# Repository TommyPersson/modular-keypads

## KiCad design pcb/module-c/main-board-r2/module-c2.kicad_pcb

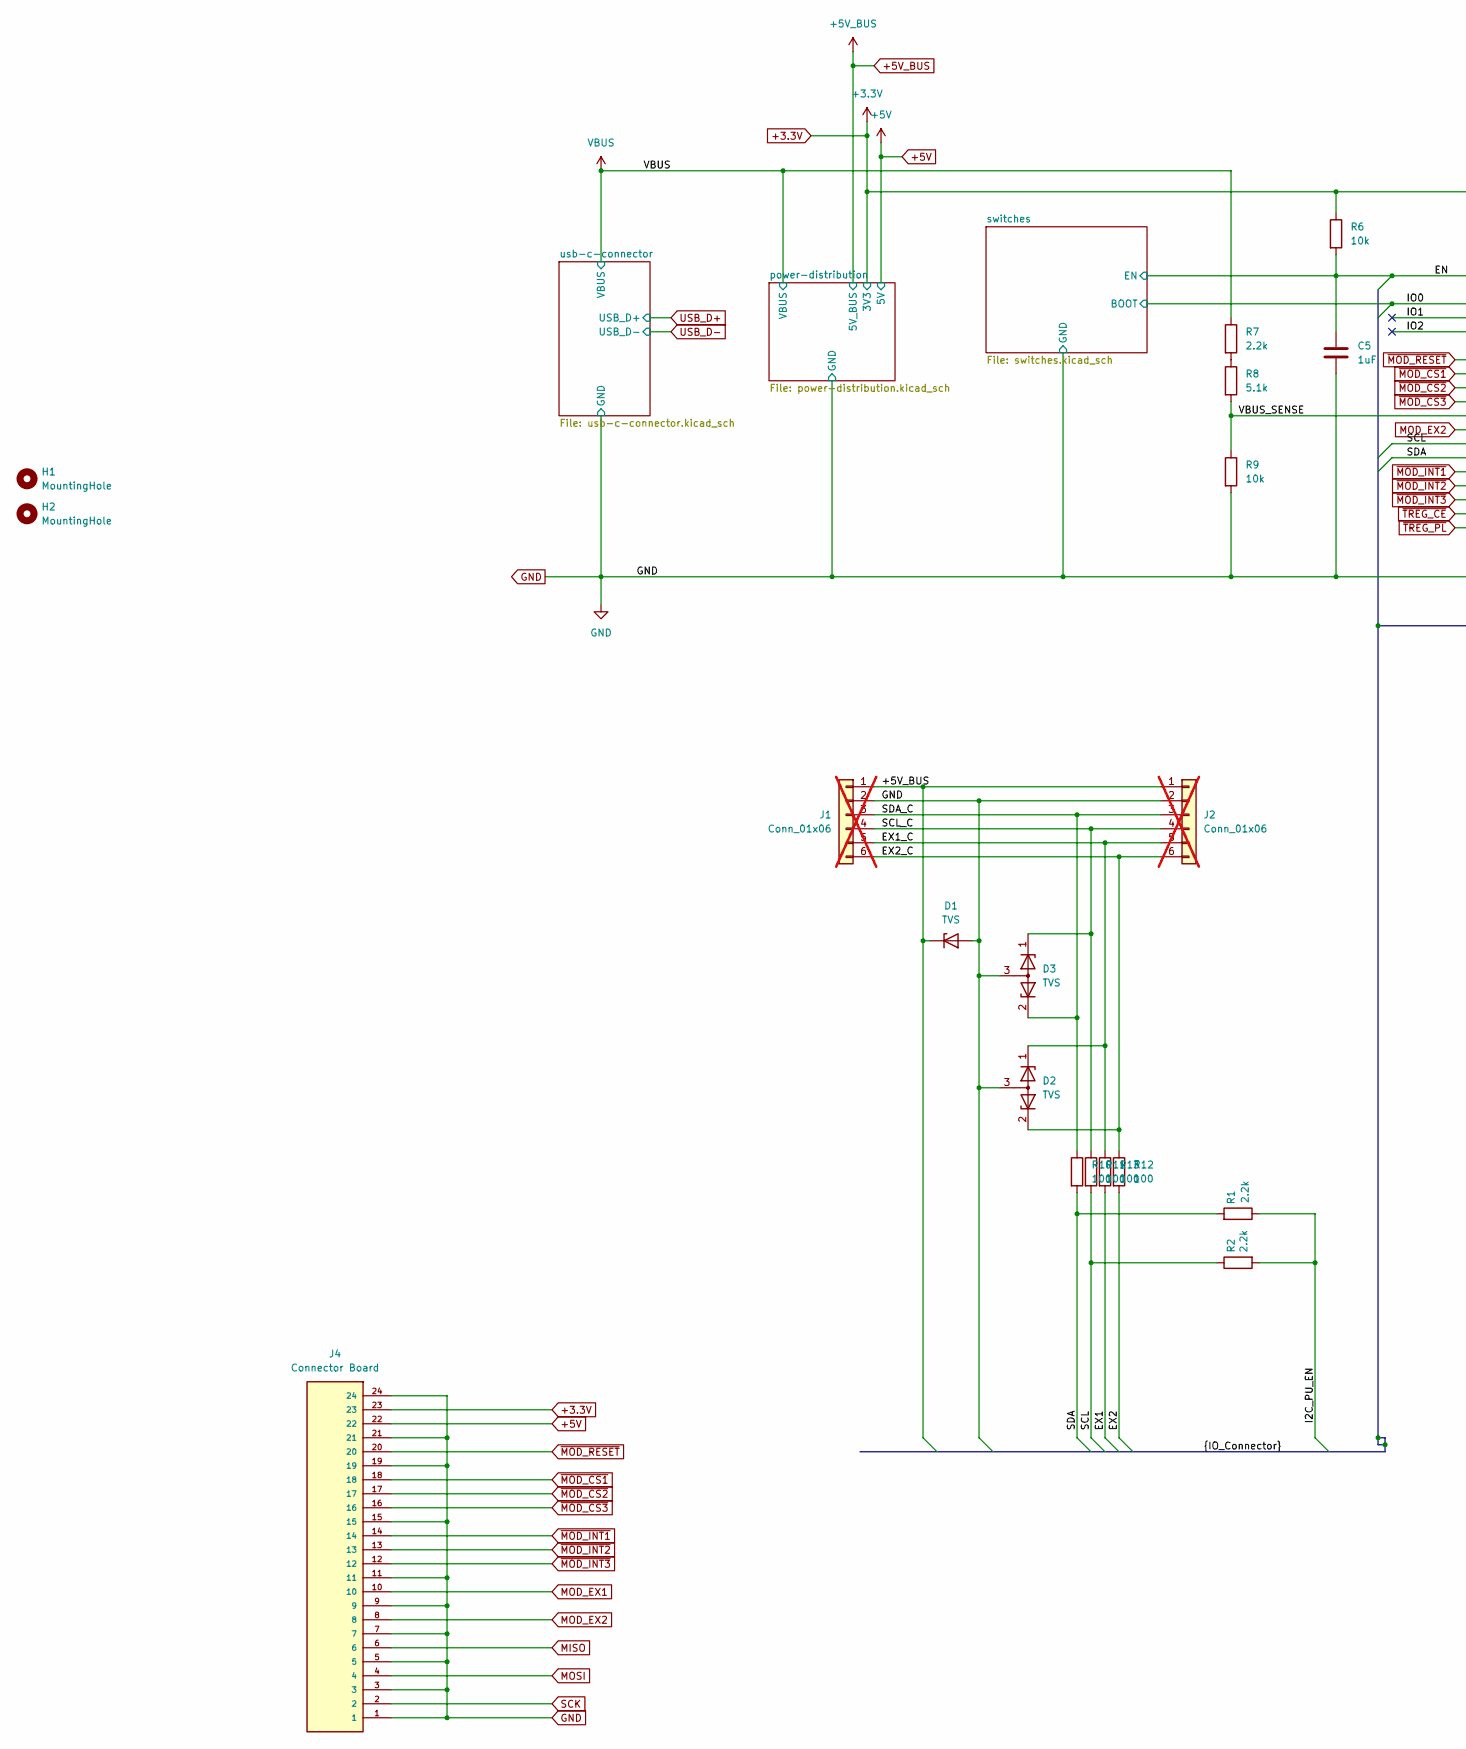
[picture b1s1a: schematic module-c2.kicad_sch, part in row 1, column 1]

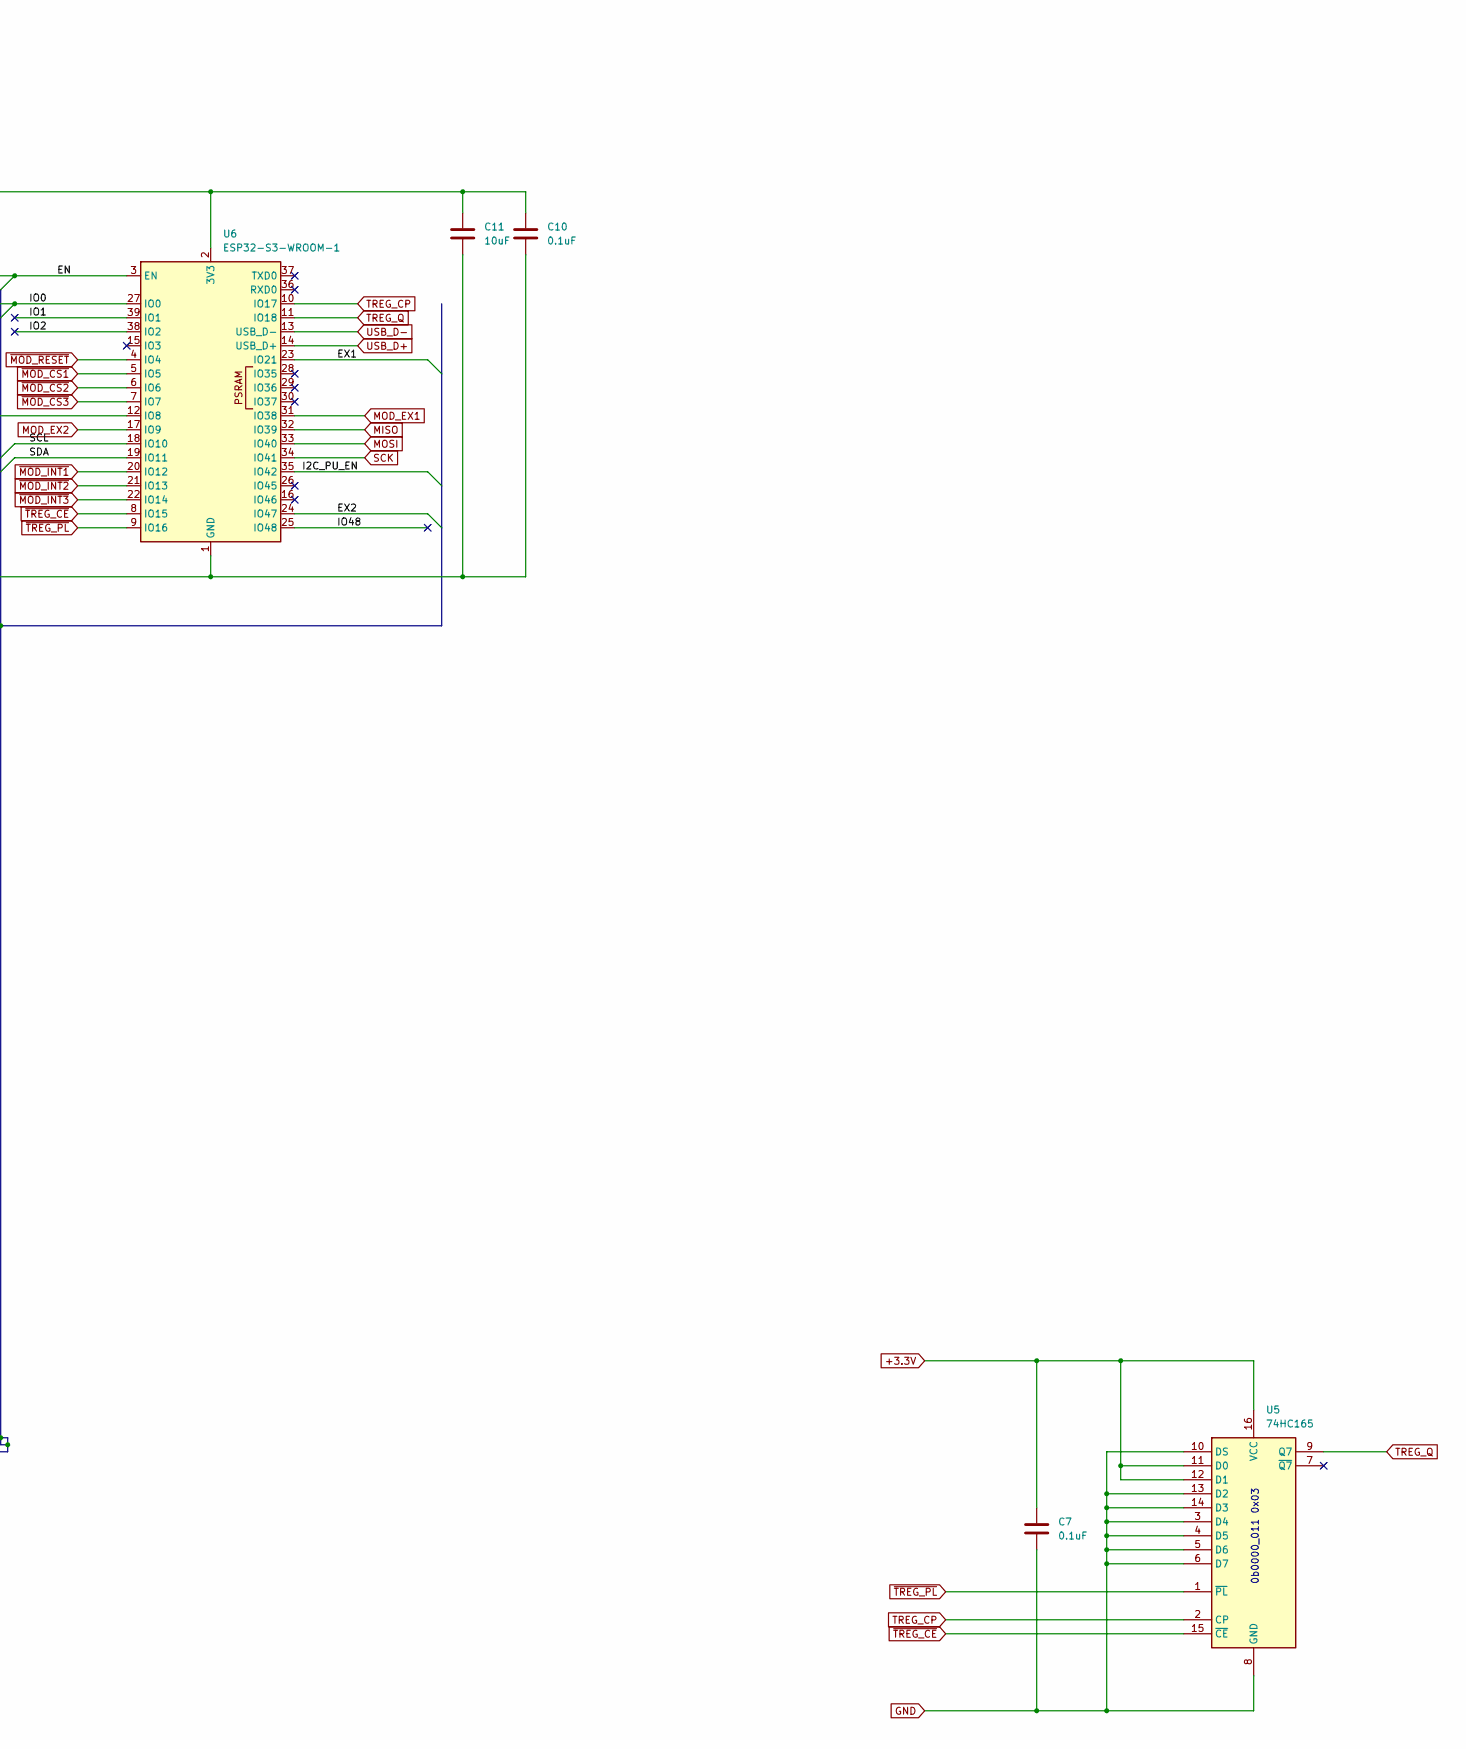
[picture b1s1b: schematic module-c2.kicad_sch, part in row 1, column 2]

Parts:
C5: 1uF; C_0805_2012Metric
C7, C10: 0.1uF; C_0603_1608Metric
C11: 10uF; C_0805_2012Metric
D1: TVS; Nexperia_CFP3_SOD-123W
D2, D3: TVS; SOT-723
H1, H2: MountingHole; MountingHole_2.2mm_M2
J1: Conn_01x06; PinSocket_1x06_P2.54mm_MagPogoHor_R; not fitted
J2: Conn_01x06; PinSocket_1x06_P2.54mm_MagPogoHor; not fitted
J4: Connector Board; AMPHENOL_F3311A7H121024E200; PARTREV A
R1, R2, R7: 2.2k; R_0603_1608Metric
R6, R9: 10k; R_0603_1608Metric
R8: 5.1k; R_0603_1608Metric
R10, R11, R12, R13: 100; R_0603_1608Metric
U5: 74HC165; DHVQFN-16-1EP_2.5x3.5mm_P0.5mm_EP1x2mm
U6: ESP32-S3-WROOM-1; ESP32-S3-WROOM-1U

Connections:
+3.3V: C7.1, C10.1, C11.1, J4.23, R6.1, U5.11 (D0), U5.12 (D1), U5.16 (VCC), U6.2 (3V3); also elsewhere on the board
+5V: J4.22; also elsewhere on the board
+5V_BUS: D1.1 (K), J1.1, J2.1; also elsewhere on the board
/EN: C5.1, R6.2, U6.3 (EN); also elsewhere on the board
/EX1: R13.2, U6.23 (IO21)
/EX1_C: D2.1 (K), J1.5, J2.5, R13.1
/EX2: R12.2, U6.24 (IO47)
/EX2_C: D2.2 (K), J1.6, J2.6, R12.1
/I2C_PU_EN: R1.1, R2.2, U6.35 (IO42)
/IO0: U6.27 (IO0); also elsewhere on the board
/IO1: U6.39 (IO1)
/IO2: U6.38 (IO2)
/IO48: U6.25 (IO48)
/SCL: R2.1, R11.2, U6.18 (IO10)
/SCL_C: D3.1 (K), J1.4, J2.4, R11.1
/SDA: R1.2, R10.2, U6.19 (IO11)
/SDA_C: D3.2 (K), J1.3, J2.3, R10.1
/VBUS_SENSE: R8.2, R9.1, U6.12 (IO8)
GND: C5.2, C7.2, C10.2, C11.2, D1.2 (A), D2.3 (A), D3.3 (A), J1.2, J2.2, J4.1, J4.3, J4.5, J4.7, J4.9, J4.11, J4.15, J4.19, J4.21, J4.24, R9.2, U5.3 (D4), U5.4 (D5), U5.5 (D6), U5.6 (D7), U5.8 (GND), U5.10 (DS), U5.13 (D2), U5.14 (D3), U6.1 (GND), U6.40 (GND), U6.41 (GND); also elsewhere on the board
MISO: J4.6, U6.32 (IO39)
MOD_EX1: J4.10, U6.31 (IO38)
MOD_EX2: J4.8, U6.17 (IO9)
MOSI: J4.4, U6.33 (IO40)
unnamed: R7.2, R8.1
SCK: J4.2, U6.34 (IO41)
TREG_CP: U5.2 (CP), U6.10 (IO17)
TREG_Q: U5.9 (Q7), U6.11 (IO18)
USB_D+: U6.14 (USB_D+); also elsewhere on the board
USB_D-: U6.13 (USB_D-); also elsewhere on the board
VBUS: R7.1; also elsewhere on the board
~MOD_CS1: J4.18, U6.5 (IO5)
~MOD_CS2: J4.17, U6.6 (IO6)
~MOD_CS3: J4.16, U6.7 (IO7)
~MOD_INT1: J4.14, U6.20 (IO12)
~MOD_INT2: J4.13, U6.21 (IO13)
~MOD_INT3: J4.12, U6.22 (IO14)
~MOD_RESET: J4.20, U6.4 (IO4)
~TREG_CE: U5.15 (~CE), U6.8 (IO15)
~TREG_PL: U5.1 (~PL), U6.9 (IO16)

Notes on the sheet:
0b0000_011 0x03

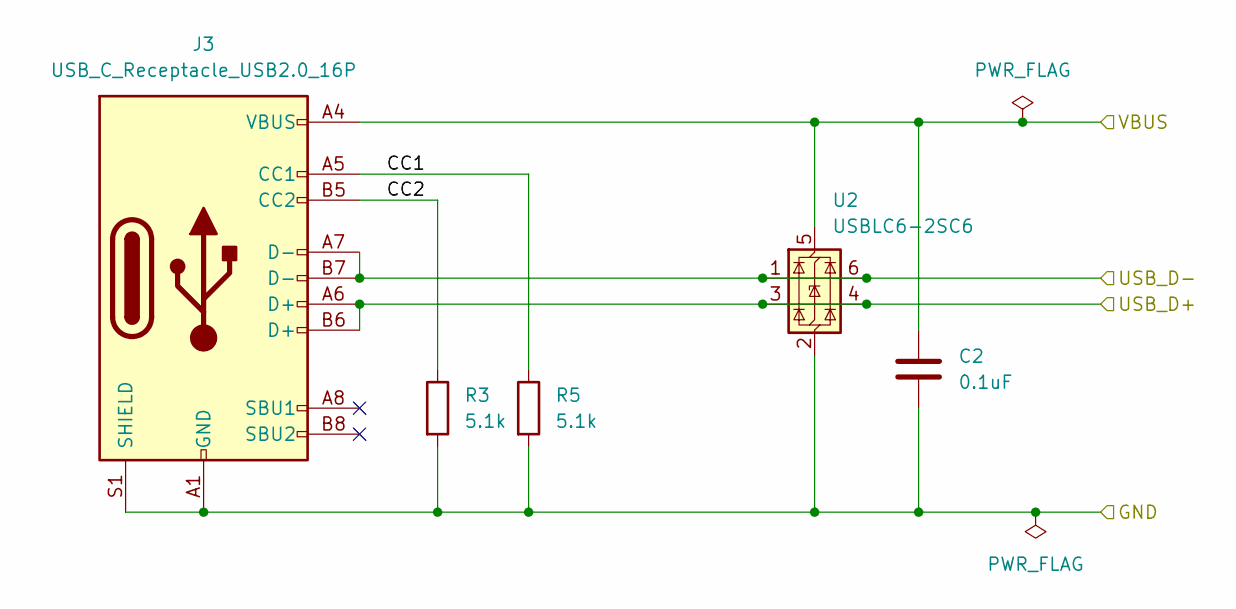
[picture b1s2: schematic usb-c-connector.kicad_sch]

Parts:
C2: 0.1uF; C_0603_1608Metric
J3: USB_C_Receptacle_USB2.0_16P; USB_C_Receptacle_GCT_USB4105-xx-A_16P_TopMnt_Horizontal
R3, R5: 5.1k; R_0603_1608Metric
U2: USBLC6-2SC6; SOT-23-6_Handsoldering

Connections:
/usb-c-connector/CC1: J3.A5 (CC1), R5.1
/usb-c-connector/CC2: J3.B5 (CC2), R3.1
GND: C2.2, J3.A1 (GND), J3.A12 (GND), J3.B1 (GND), J3.B12 (GND), J3.S1 (SHIELD), R3.2, R5.2, U2.2 (GND); also elsewhere on the board
USB_D+: J3.A6 (D+), J3.B6 (D+), U2.3 (I/O2), U2.4 (I/O2); also elsewhere on the board
USB_D-: J3.A7 (D-), J3.B7 (D-), U2.1 (I/O1), U2.6 (I/O1); also elsewhere on the board
VBUS: C2.1, J3.A4 (VBUS), J3.A9 (VBUS), J3.B4 (VBUS), J3.B9 (VBUS), U2.5 (VBUS); also elsewhere on the board

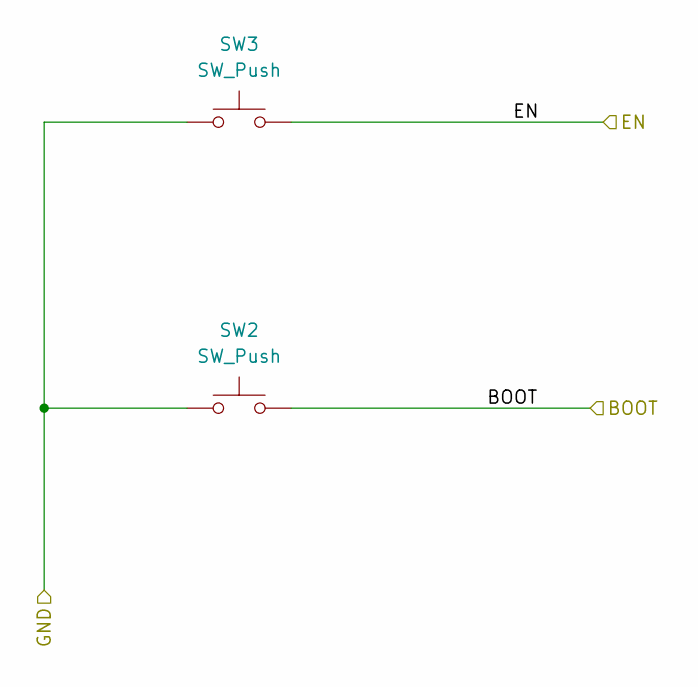
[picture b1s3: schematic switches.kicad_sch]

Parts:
SW2, SW3: SW_Push; Panasonic_EVQPUL_EVQPUC

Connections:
/EN: SW3.2; also elsewhere on the board
/IO0: SW2.2; also elsewhere on the board
GND: SW2.1, SW3.1; also elsewhere on the board

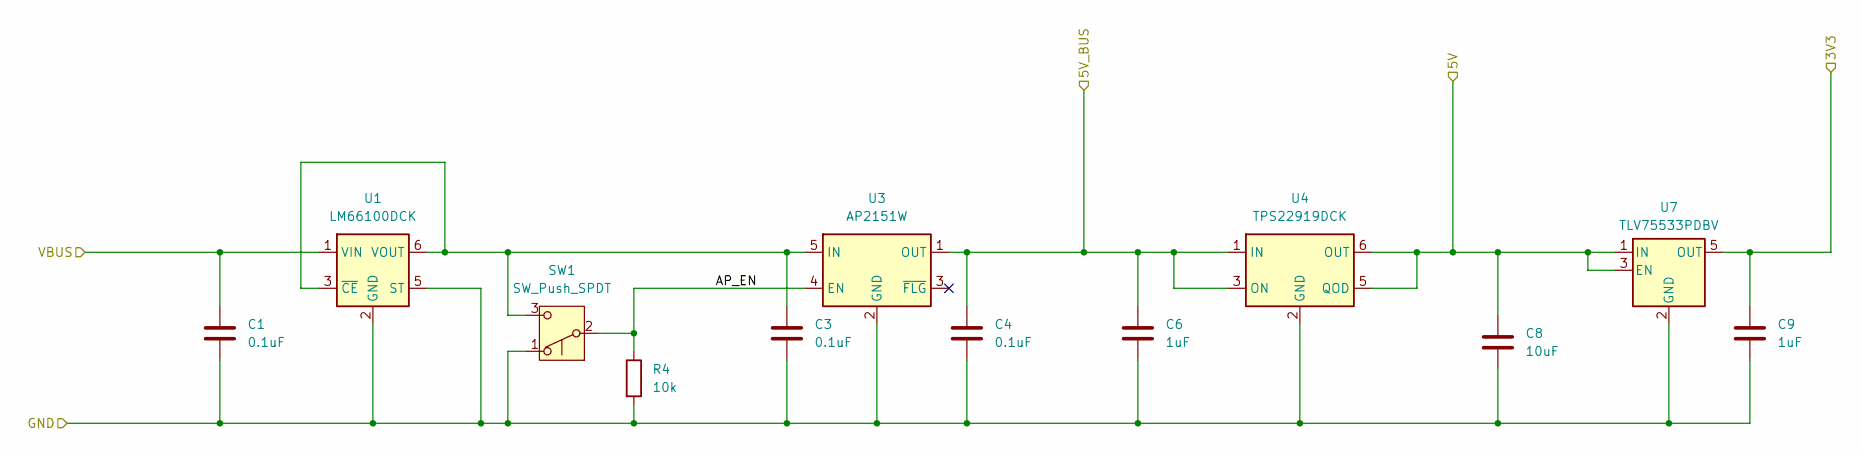
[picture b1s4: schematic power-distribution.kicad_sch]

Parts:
C1, C3, C4: 0.1uF; C_0603_1608Metric
C6, C9: 1uF; C_0805_2012Metric
C8: 10uF; C_0805_2012Metric
R4: 10k; R_0603_1608Metric
SW1: SW_Push_SPDT; SW_MSK12C02-HB
U1: LM66100DCK; SOT-363_SC-70-6
U3: AP2151W; SOT-23-5_HandSoldering
U4: TPS22919DCK; SOT-363_SC-70-6
U7: TLV75533PDBV; SOT-23-5

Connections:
+3.3V: C9.1, U7.5 (OUT); also elsewhere on the board
+5V: C8.1, U4.5 (QOD), U4.6 (OUT), U7.1 (IN), U7.3 (EN); also elsewhere on the board
+5V_BUS: C4.1, C6.1, U3.1 (OUT), U4.1 (IN), U4.3 (ON); also elsewhere on the board
/power-distribution/AP_EN: R4.1, SW1.2 (B), U3.4 (EN)
GND: C1.2, C3.2, C4.2, C6.2, C8.2, C9.2, R4.2, SW1.1 (A), U1.2 (GND), U1.5 (ST), U3.2 (GND), U4.2 (GND), U7.2 (GND); also elsewhere on the board
unnamed: C3.1, SW1.3 (C), U1.3 (~CE), U1.6 (VOUT), U3.5 (IN)
VBUS: C1.1, U1.1 (VIN); also elsewhere on the board

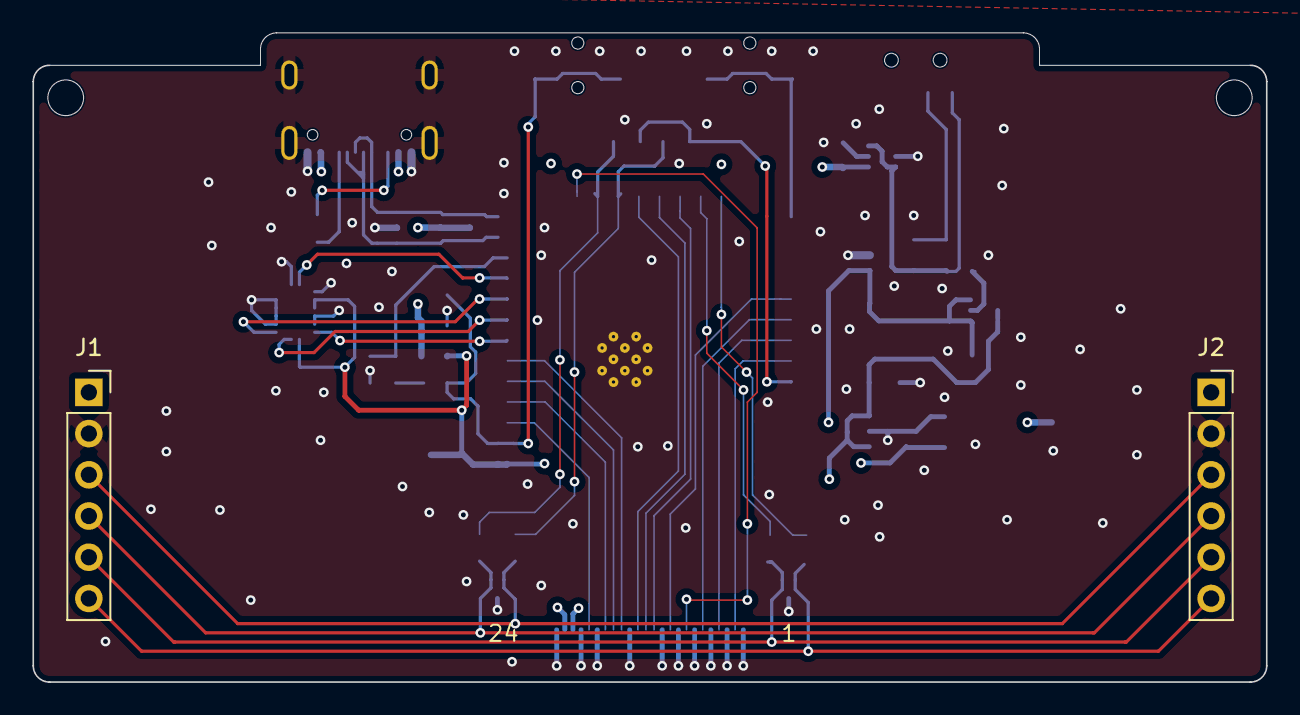
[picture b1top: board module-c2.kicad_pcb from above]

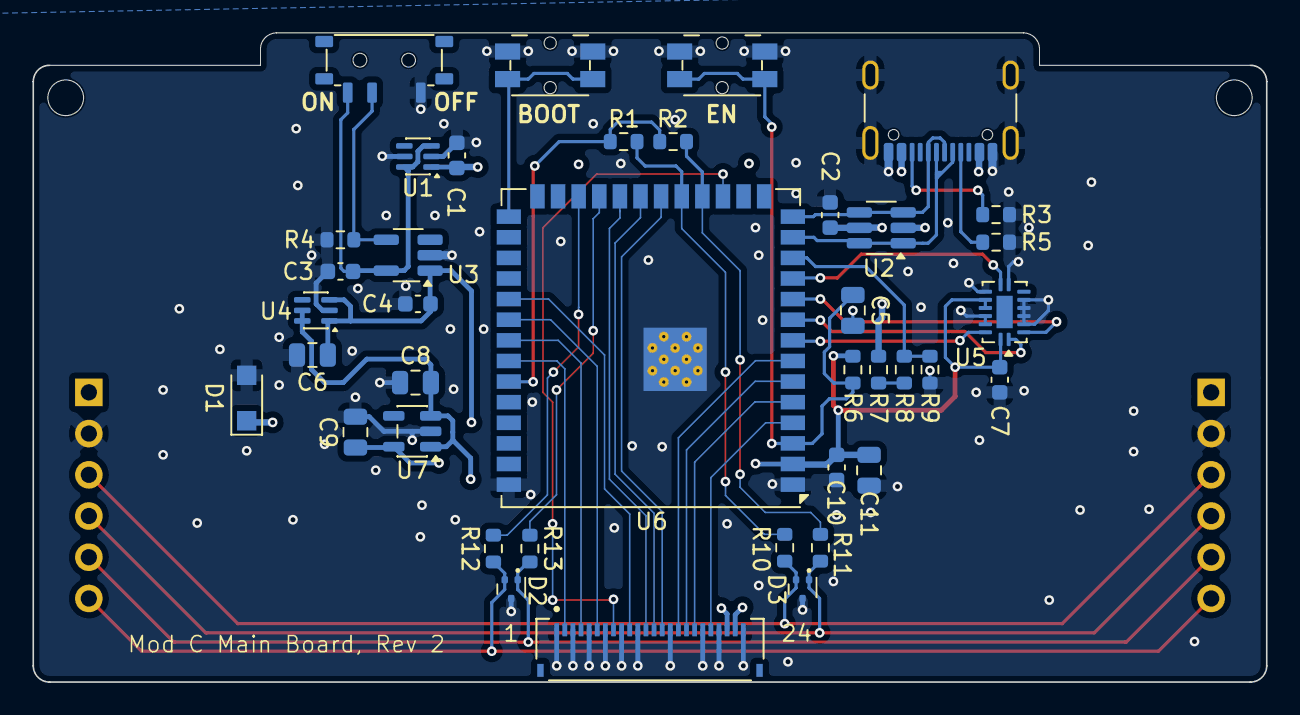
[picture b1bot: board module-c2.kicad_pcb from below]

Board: 4 copper layers, 76.0 x 40.0 mm, 43 parts (39 on the bottom side), 40 nets.

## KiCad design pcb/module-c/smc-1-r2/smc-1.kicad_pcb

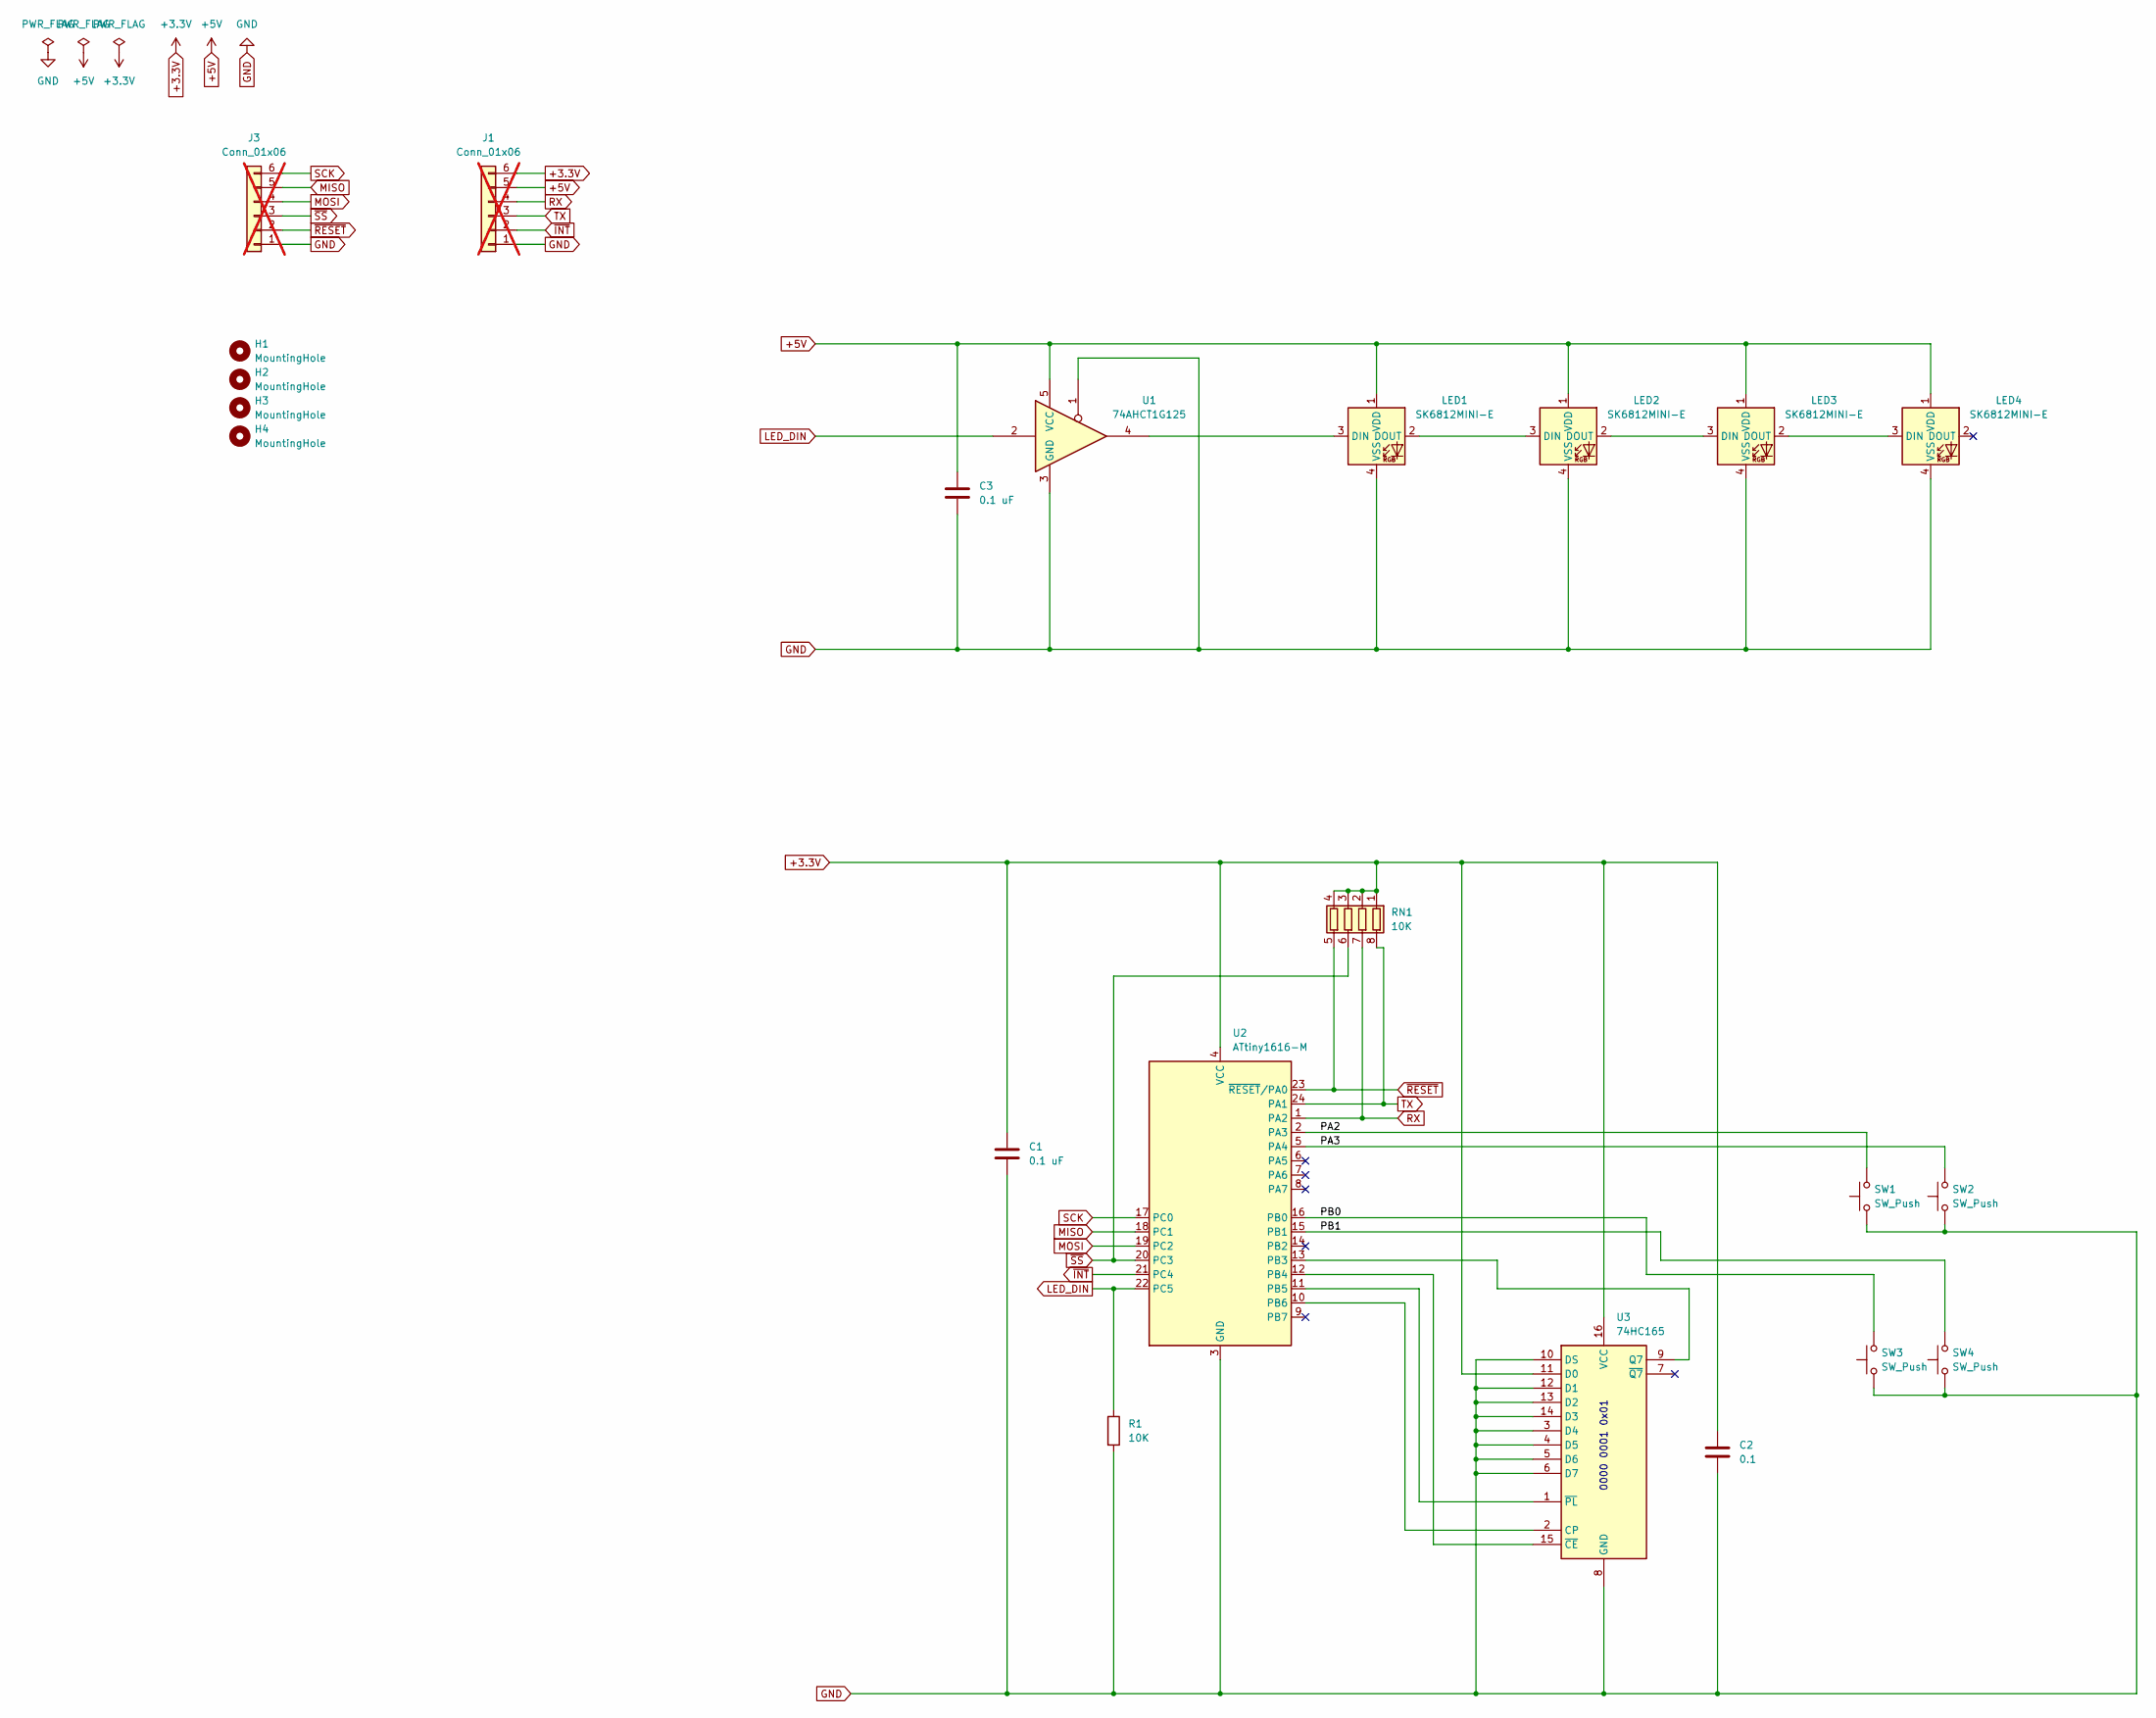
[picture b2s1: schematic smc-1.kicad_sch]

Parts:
C1, C3: 0.1 uF; C_0603_1608Metric
C2: 0.1; C_0603_1608Metric
H1, H2, H3, H4: MountingHole; MountingHole_2.2mm_M2
J1, J3: Conn_01x06; PinHeader_1x06_P2.54mm_Vertical; not fitted
LED1, LED2, LED3, LED4: SK6812MINI-E; LED_choc_6028R-ROT
R1: 10K; R_0603_1608Metric
RN1: 10K; R_Array_Concave_4x0603
SW1, SW2, SW3, SW4: SW_Push; SW_Hotswap_Kailh_Choc_V1_1.50u
U1: 74AHCT1G125; SOT-353_SC-70-5
U2: ATtiny1616-M; QFN-24-1EP_4x4mm_P0.5mm_EP2.6x2.6mm
U3: 74HC165; DHVQFN-16-1EP_2.5x3.5mm_P0.5mm_EP1x2mm

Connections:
+3.3V: C1.1, C2.1, J1.6, RN1.1 (R1.1), RN1.2 (R2.1), RN1.3 (R3.1), RN1.4 (R4.1), U2.4 (VCC), U3.11 (D0), U3.16 (VCC)
+5V: C3.1, J1.5, LED1.1 (VDD), LED2.1 (VDD), LED3.1 (VDD), LED4.1 (VDD), U1.5 (VCC)
/PA2: SW1.2, U2.2 (PA3)
/PA3: SW2.2, U2.5 (PA4)
/PB0: SW3.2, U2.16 (PB0)
/PB1: SW4.2, U2.15 (PB1)
GND: C1.2, C2.2, C3.2, J1.1, J3.1, LED1.4 (VSS), LED2.4 (VSS), LED3.4 (VSS), LED4.4 (VSS), R1.2, SW1.1, SW2.1, SW3.1, SW4.1, U1.1, U1.3 (GND), U2.3 (GND), U2.25 (GND), U3.3 (D4), U3.4 (D5), U3.5 (D6), U3.6 (D7), U3.8 (GND), U3.10 (DS), U3.12 (D1), U3.13 (D2), U3.14 (D3)
LED_DIN: R1.1, U1.2, U2.22 (PC5)
MISO: J3.5, U2.18 (PC1)
MOSI: J3.4, U2.19 (PC2)
unnamed: LED1.3 (DIN), U1.4
unnamed: LED1.2 (DOUT), LED2.3 (DIN)
unnamed: LED2.2 (DOUT), LED3.3 (DIN)
unnamed: LED3.2 (DOUT), LED4.3 (DIN)
unnamed: U2.13 (PB3), U3.9 (Q7)
unnamed: U2.12 (PB4), U3.15 (~CE)
unnamed: U2.11 (PB5), U3.1 (~PL)
unnamed: U2.10 (PB6), U3.2 (CP)
RX: J1.4, RN1.7 (R2.2), U2.1 (PA2)
SCK: J3.6, U2.17 (PC0)
TX: J1.3, RN1.8 (R1.2), U2.24 (PA1)
~INT: J1.2, U2.21 (PC4)
~RESET: J3.2, RN1.5 (R4.2), U2.23 (~RESET/PA0)
~SS: J3.3, RN1.6 (R3.2), U2.20 (PC3)

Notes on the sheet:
0000 0001 0x01

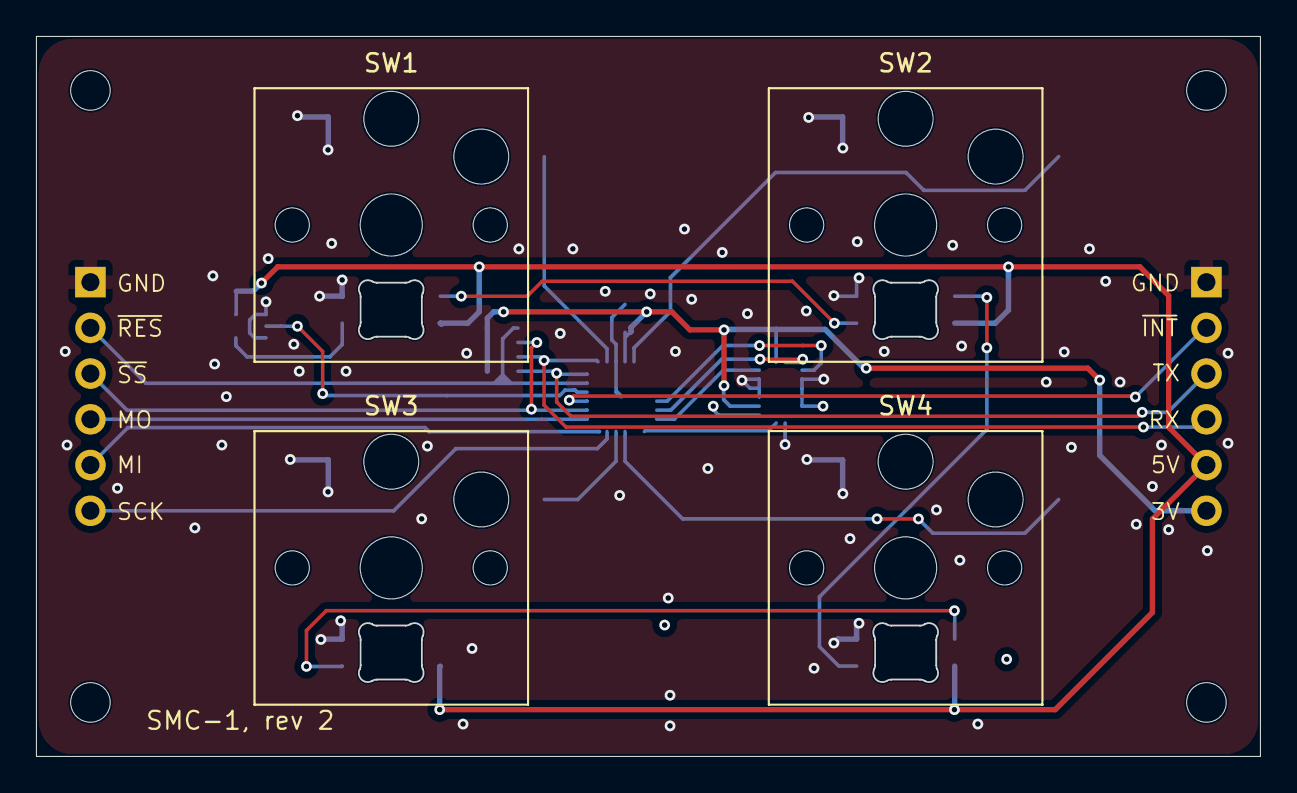
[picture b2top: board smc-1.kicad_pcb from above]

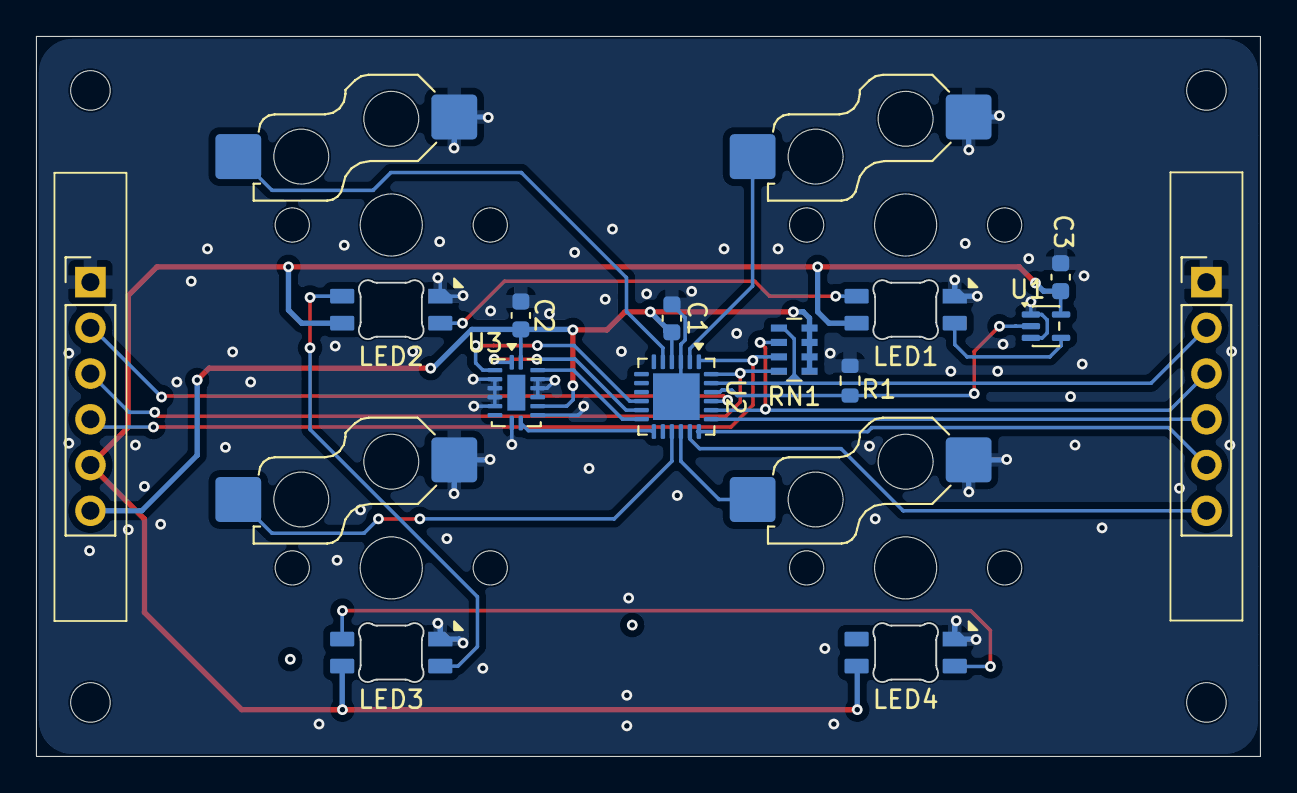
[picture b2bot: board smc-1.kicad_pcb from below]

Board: 4 copper layers, 68.0 x 40.0 mm, 22 parts (14 on the bottom side), 24 nets.

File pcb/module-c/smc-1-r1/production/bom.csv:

Designator,Footprint,Quantity,Value,LCSC Part #
"C1, C2",0603,2,0.1,
C3,0603,1,0.1 uF,
"J1, J3",PinHeader_1x06_P2.54mm_Vertical,2,Conn_01x06,
"LED1, LED2, LED3, LED4, LED5, LED6",LED_choc_6028R-ROT,6,SK6812MINI-E,
"SW1, SW2, SW3, SW4, SW5, SW6",SW_Hotswap_Kailh_Choc_V1_1.00u,6,SW_Push,
U1,SOT-353_SC-70-5,1,74AHCT1G125,
U2,QFN-24-1EP_4x4mm_P0.5mm_EP2.6x2.6mm,1,ATtiny1616-M,
U3,DHVQFN-16-1EP_2.5x3.5mm_P0.5mm_EP1x2mm,1,74HC165,

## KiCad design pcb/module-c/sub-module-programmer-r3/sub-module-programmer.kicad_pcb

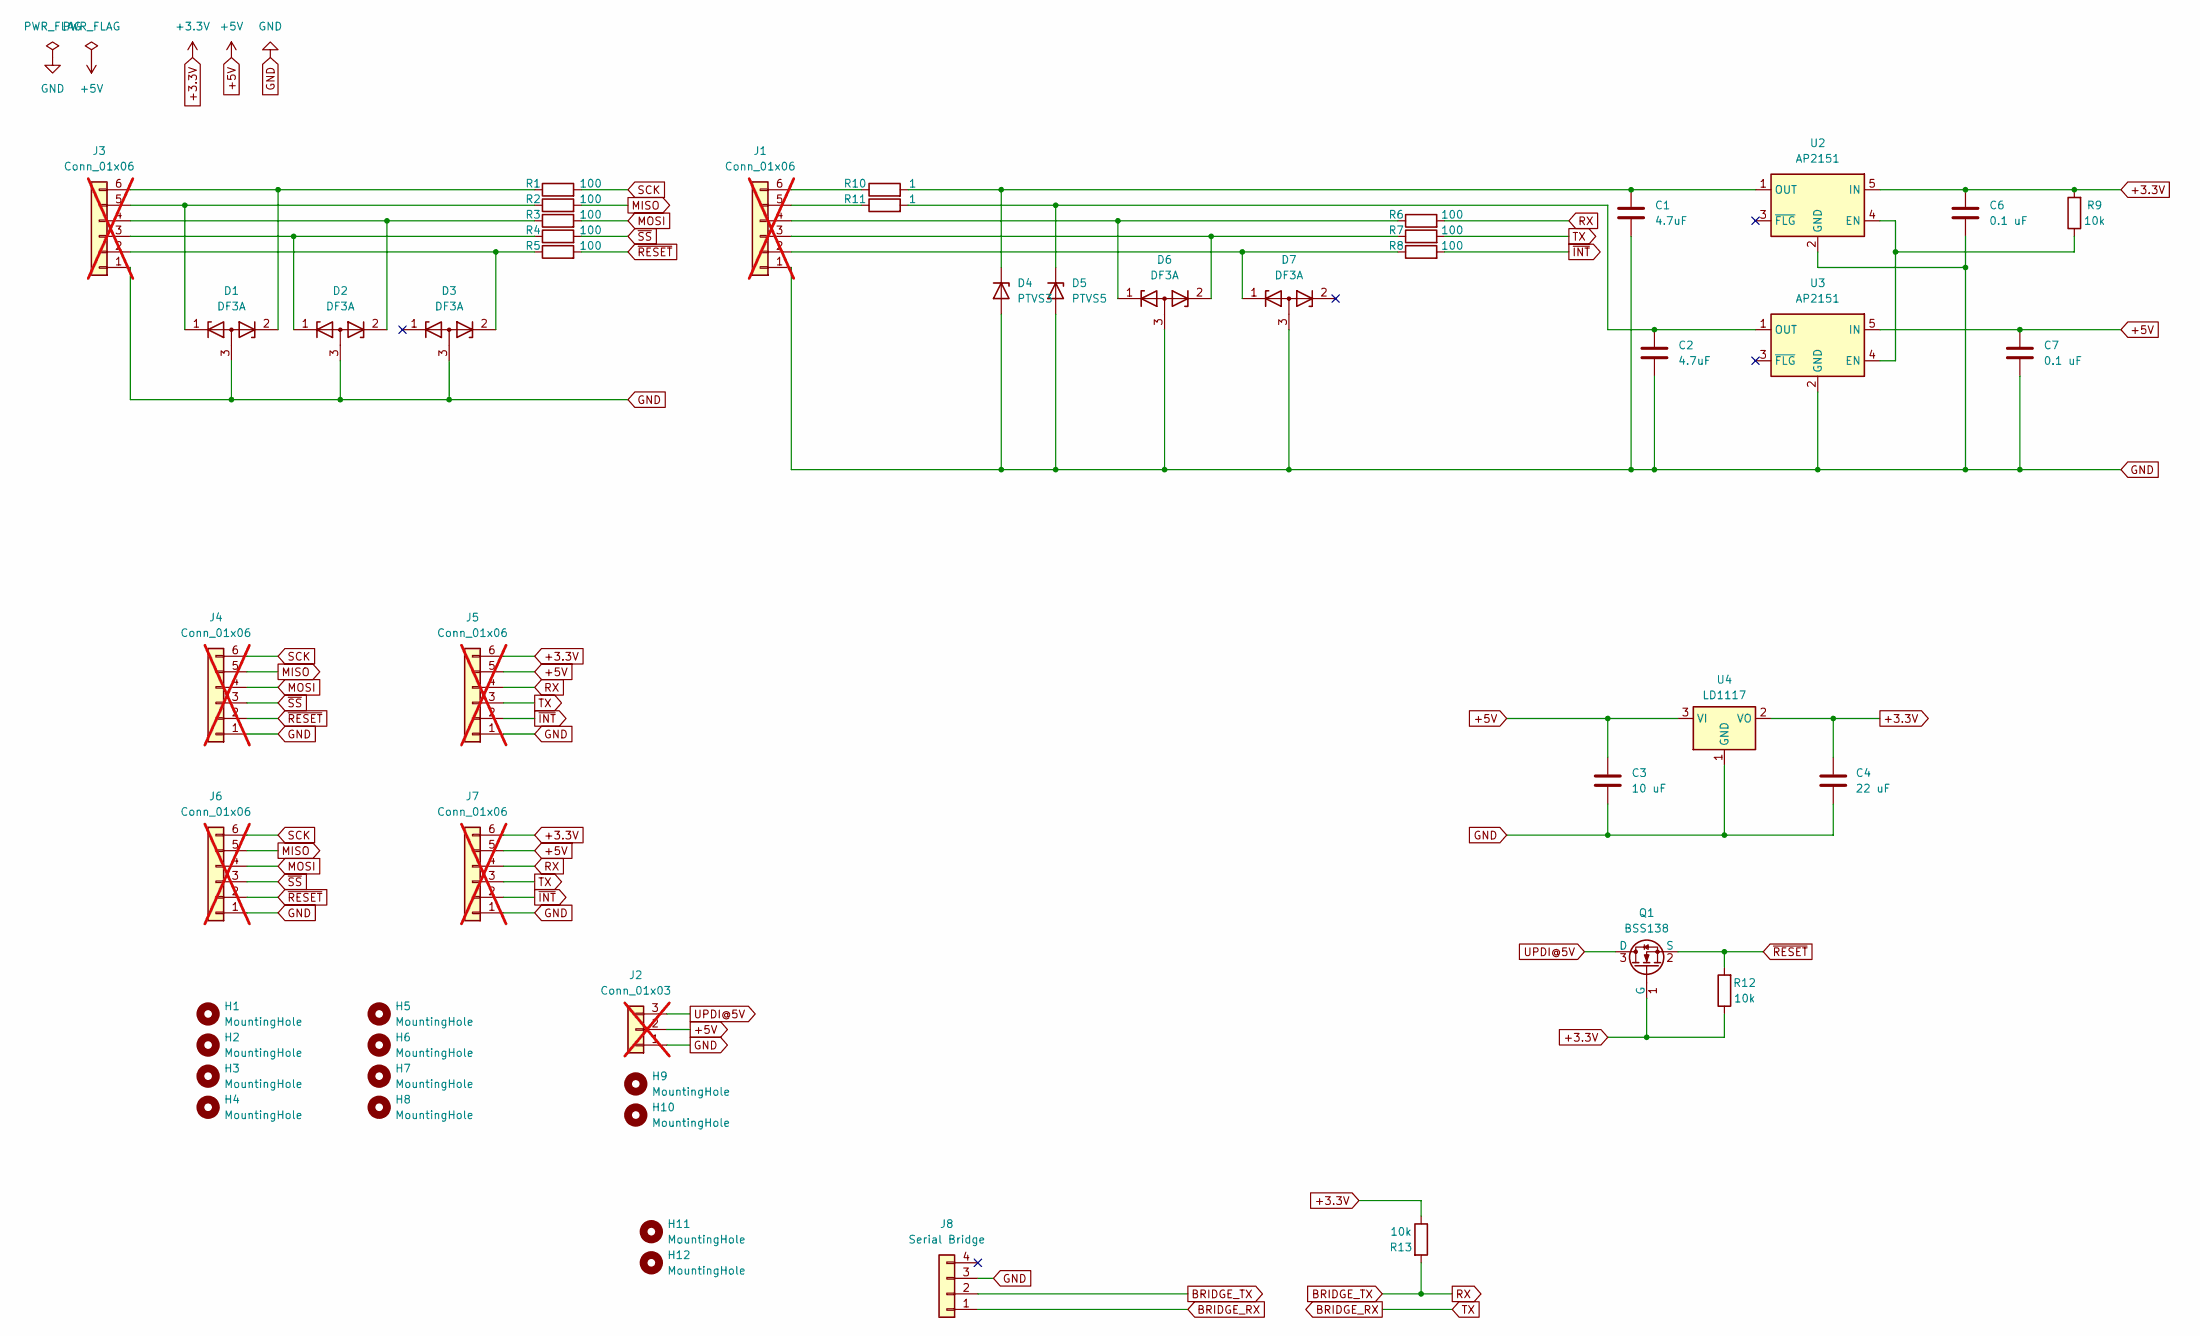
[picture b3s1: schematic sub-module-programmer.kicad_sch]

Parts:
C1, C2: 4.7uF; C_0805_2012Metric
C3: 10 uF; C_1206_3216Metric
C4: 22 uF; C_1206_3216Metric
C6, C7: 0.1 uF; C_0603_1608Metric
D1, D2, D3, D6, D7: DF3A; SOT-723
D4: PTVS3; Nexperia_CFP3_SOD-123W
D5: PTVS5; Nexperia_CFP3_SOD-123W
H1, H2, H3, H4, H5, H6, H7, H8, H9, H10, H11, H12: MountingHole; MountingHole_2.2mm_M2
J1, J3, J4, J5, J6, J7: Conn_01x06; PinHeader_1x06_P2.54mm_Vertical; not fitted
J2: Conn_01x03; PinHeader_1x03_P2.54mm_Vertical; not fitted
J8: Serial Bridge; PinHeader_1x04_P2.54mm_Vertical
Q1: BSS138; SOT-23
R1, R2, R3, R4, R5, R6, R7, R8: 100; R_0603_1608Metric
R9, R12, R13: 10k; R_0603_1608Metric
R10, R11: 1; R_0805_2012Metric
U2, U3: AP2151; SOT-23-5
U4: LD1117; SOT-223-3_TabPin2

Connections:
+3.3V: C4.1, C6.1, J5.6, J7.6, Q1.1 (G), R9.2, R12.1, R13.1, U2.5 (IN), U4.2 (VO)
+5V: C3.1, C7.1, J2.2, J5.5, J7.5, U3.5 (IN), U4.3 (VI)
BRIDGE_RX: J5.3, J7.3, J8.1, R7.2
BRIDGE_TX: J5.4, J7.4, J8.2, R6.2, R13.2
GND: C1.2, C2.2, C3.2, C4.2, C6.2, C7.2, D1.3 (A), D2.3 (A), D3.3 (A), D4.2 (A), D5.2 (A), D6.3 (A), D7.3 (A), J1.1, J2.1, J3.1, J4.1, J5.1, J6.1, J7.1, J8.3, U2.2 (GND), U3.2 (GND), U4.1 (GND)
MISO: J4.5, J6.5, R2.2
MOSI: J4.4, J6.4, R3.2
unnamed: C1.1, D4.1 (K), R10.2, U2.1 (OUT)
unnamed: C2.1, D5.1 (K), R11.2, U3.1 (OUT)
unnamed: D7.1 (K), J1.2, R8.1
unnamed: D6.2 (K), J1.3, R7.1
unnamed: D6.1 (K), J1.4, R6.1
unnamed: J1.5, R11.1
unnamed: J1.6, R10.1
unnamed: D3.2 (K), J3.2, R5.1
unnamed: D2.1 (K), J3.3, R4.1
unnamed: D2.2 (K), J3.4, R3.1
unnamed: D1.1 (K), J3.5, R2.1
unnamed: D1.2 (K), J3.6, R1.1
unnamed: R9.1, U2.4 (EN), U3.4 (EN)
SCK: J4.6, J6.6, R1.2
UPDI@5V: J2.3, Q1.3 (D)
~INT: J5.2, J7.2, R8.2
~RESET: J4.2, J6.2, Q1.2 (S), R5.2, R12.2
~SS: J4.3, J6.3, R4.2
